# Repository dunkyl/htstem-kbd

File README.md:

# HTSTEM Keyboard

CAD files for the HTSTEM keyboard.

## Macro12

Test board for the project. 12 keys, 12 addressible LEDs, and rotary encoder. First time I've actually gone through with ordering a PCB to be made.

Source code for firmware is at [another repo](https://github.com/dunkyl/dunkylmacro12).

BOM for macro12:

| Quantity | Description | Link | Note |
| --- | --- | --- | --- |
| 1 | Teensy 2.0 | https://www.pjrc.com/store/teensy.html | Or any compatible microcontroller. I used an [Elite-C from Keebio](https://keeb.io/collections/diy-parts/products/elite-c-low-profile-version-usb-c-pro-micro-replacement-atmega32u4) |
| 1 | PEC11 12mm Rotary Encoder | https://www.digikey.com/en/products/detail/bourns-inc/PEC11L-4220F-S0015/2440942 | |
| 1 | Knob | https://www.digikey.com/en/products/detail/sparkfun-electronics/COM-10001/7229870 | Any knob really |
| 12 | Addressible LED SK6812MINI-E Reverse Mount | https://www.adafruit.com/product/4960 | 10 pack so buy qty 2 |
| 12 | Diode 1N4148FS-ND | https://www.digikey.com/en/products/detail/onsemi/1N4148/458603?s=N4IgTCBcDaIIwDkAsckA4BiBlAtAgIiALoC%2BQA | Or similiar |
| 12 | Key Switch | - | Your choice |
| 12 | Key Cap | - | Your choice |
| 1 | 3D Printed Case | - | Source files here |
| 1 | PCB | - | Source files here |
| 4 | Rubber Feet | https://www.adafruit.com/product/550 | Optional |
| - | Some tape | - | To hold the case halves together. |

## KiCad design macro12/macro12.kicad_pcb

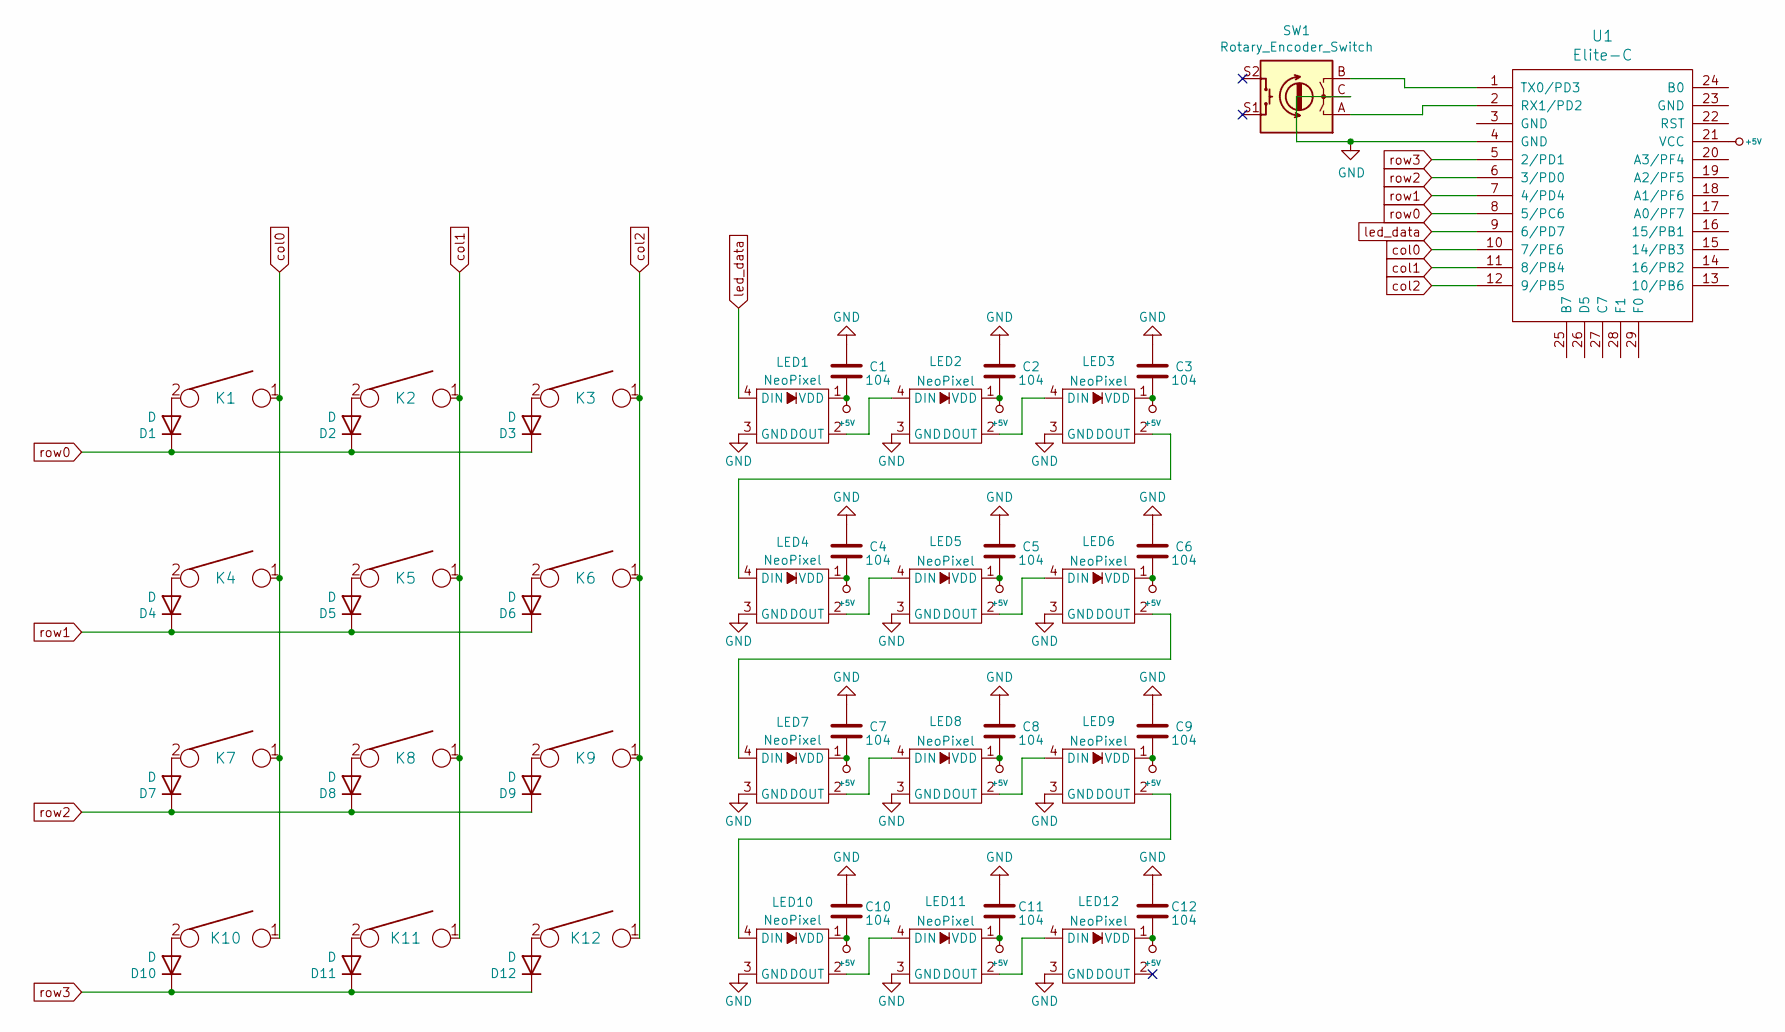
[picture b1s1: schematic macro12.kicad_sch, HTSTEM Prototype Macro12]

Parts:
C1, C2, C3, C4, C5, C6, C7, C8, C9, C10, C11, C12: 104; C_0805_2012Metric_Pad1.18x1.45mm_HandSolder
D1, D2, D3, D4, D5, D6, D7, D8, D9, D10, D11, D12: D; D_SOD123_axial
K1, K2, K3, K4, K5, K6, K7, K8, K9, K10, K11, K12: KEYSW; Mx_Alps_100
LED1, LED2, LED3, LED4, LED5, LED6, LED7, LED8, LED9, LED10, LED11, LED12: NeoPixel; Adafruit NeoPixel SK6812_E
SW1: Rotary_Encoder_Switch; RotaryEncoder_Alps_EC11E-Switch_Vertical_H20mm
U1: Elite-C; Elite-C-castellated-29pin-holes

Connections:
+5V: C1.1, C2.1, C3.1, C4.1, C5.1, C6.1, C7.1, C8.1, C9.1, C10.1, C11.1, C12.1, LED1.1 (VDD), LED2.1 (VDD), LED3.1 (VDD), LED4.1 (VDD), LED5.1 (VDD), LED6.1 (VDD), LED7.1 (VDD), LED8.1 (VDD), LED9.1 (VDD), LED10.1 (VDD), LED11.1 (VDD), LED12.1 (VDD), U1.21 (VCC)
GND: C1.2, C2.2, C3.2, C4.2, C5.2, C6.2, C7.2, C8.2, C9.2, C10.2, C11.2, C12.2, LED1.3 (GND), LED2.3 (GND), LED3.3 (GND), LED4.3 (GND), LED5.3 (GND), LED6.3 (GND), LED7.3 (GND), LED8.3 (GND), LED9.3 (GND), LED10.3 (GND), LED11.3 (GND), LED12.3 (GND), SW1.C, U1.4 (GND)
unnamed: D1.2 (A), K1.2
unnamed: D2.2 (A), K2.2
unnamed: D3.2 (A), K3.2
unnamed: D4.2 (A), K4.2
unnamed: D5.2 (A), K5.2
unnamed: D6.2 (A), K6.2
unnamed: D7.2 (A), K7.2
unnamed: D8.2 (A), K8.2
unnamed: D9.2 (A), K9.2
unnamed: D10.2 (A), K10.2
unnamed: D11.2 (A), K11.2
unnamed: D12.2 (A), K12.2
unnamed: LED1.2 (DOUT), LED2.4 (DIN)
unnamed: LED2.2 (DOUT), LED3.4 (DIN)
unnamed: LED3.2 (DOUT), LED4.4 (DIN)
unnamed: LED4.2 (DOUT), LED5.4 (DIN)
unnamed: LED5.2 (DOUT), LED6.4 (DIN)
unnamed: LED6.2 (DOUT), LED7.4 (DIN)
unnamed: LED7.2 (DOUT), LED8.4 (DIN)
unnamed: LED8.2 (DOUT), LED9.4 (DIN)
unnamed: LED10.2 (DOUT), LED11.4 (DIN)
unnamed: LED9.2 (DOUT), LED10.4 (DIN)
unnamed: LED11.2 (DOUT), LED12.4 (DIN)
unnamed: SW1.A, U1.2 (RX1/PD2)
unnamed: SW1.B, U1.1 (TX0/PD3)
col0: K1.1, K4.1, K7.1, K10.1, U1.10 (7/PE6)
col1: K2.1, K5.1, K8.1, K11.1, U1.11 (8/PB4)
col2: K3.1, K6.1, K9.1, K12.1, U1.12 (9/PB5)
led_data: LED1.4 (DIN), U1.9 (6/PD7)
row0: D1.1 (K), D2.1 (K), D3.1 (K), U1.8 (5/PC6)
row1: D4.1 (K), D5.1 (K), D6.1 (K), U1.7 (4/PD4)
row2: D7.1 (K), D8.1 (K), D9.1 (K), U1.6 (3/PD0)
row3: D10.1 (K), D11.1 (K), D12.1 (K), U1.5 (2/PD1)

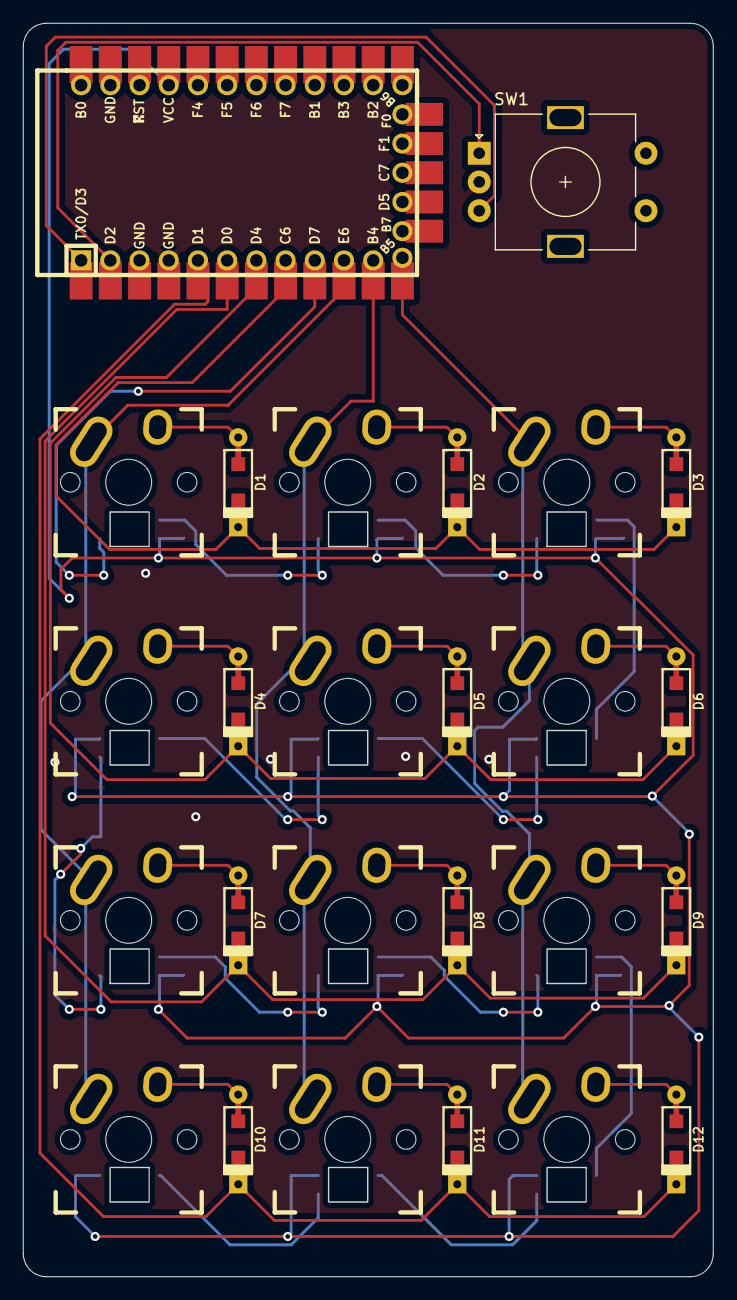
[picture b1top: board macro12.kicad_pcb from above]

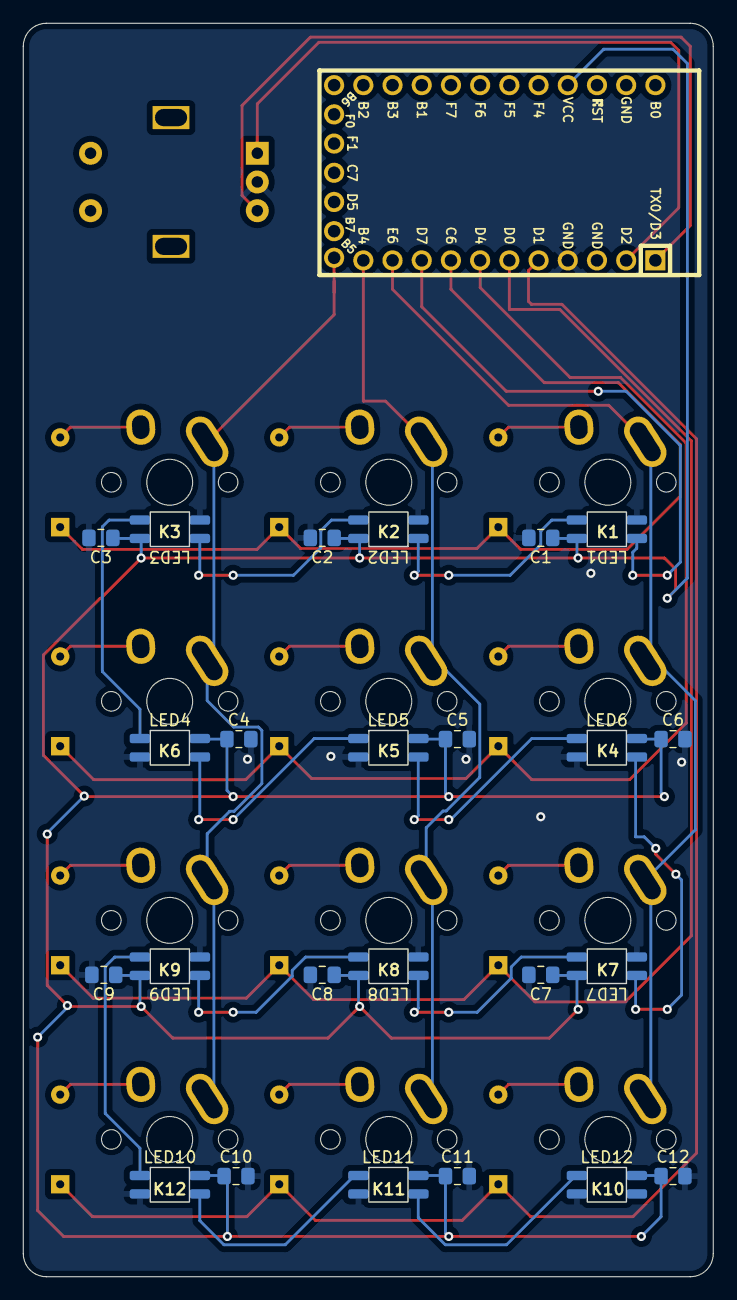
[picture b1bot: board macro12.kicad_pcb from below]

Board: 2 copper layers, 59.9 x 108.9 mm, 50 parts (24 on the bottom side), 35 nets.

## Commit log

2023-01-18 shorten table
2023-01-18 add link to firmware
